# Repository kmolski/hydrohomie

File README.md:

# hydrohomie

The smart drink coaster that lets you gather, view and analyze data on your water drinking habits.

The coaster device, based on the ESP32 MCU, uses a load sensor to measure the volume of water consumed,
which is then (optionally) sent over Wi-Fi & MQTT to the web application for storage and presentation purposes.

This started out as my 5th semester project for the Microprocessor and Embedded Systems course, for which I
prepared the hardware and firmware components. The web application was created later, primarily as a means to
get some practice with new Java features and popular libraries, like Spring Integration/Security and Mockito.

Project components
------------------

- [Hardware](./hardware) - board & logic schematics in PDF & Autodesk EAGLE files
- [Firmware](./firmware) - firmware for the ESP32 chip, based on the Arduino platform
- [Web application](./web-app) - (optional) Spring Boot web app, provides coaster management & data visualization functionality

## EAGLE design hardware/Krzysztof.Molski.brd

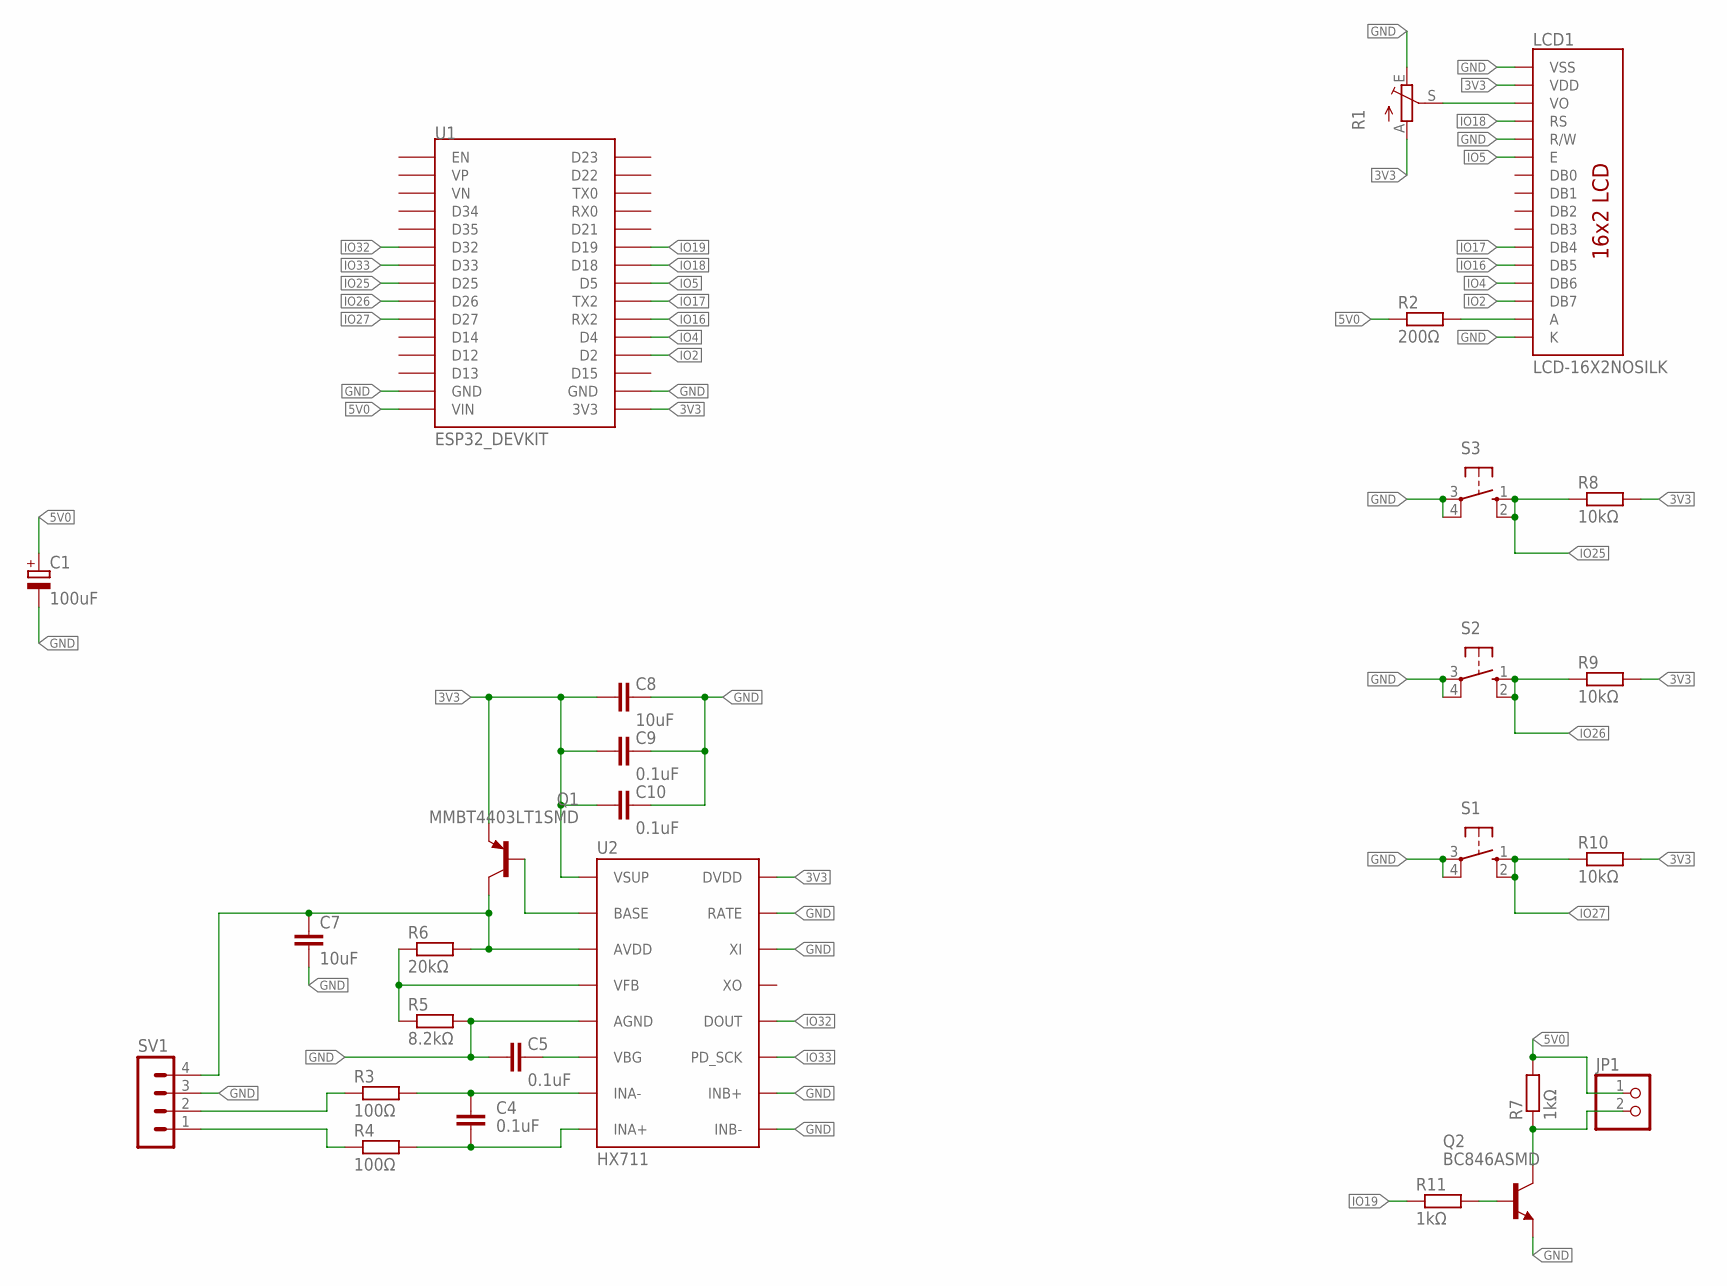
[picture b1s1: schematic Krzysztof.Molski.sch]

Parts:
C1: 100uF; CT3528
C4, C5, C9, C10: 0.1uF; C1206
C7, C8: 10uF; C1206
JP1: PINHD-1X2; 1X02
LCD1: LCD-16X2NOSILK; LCD-16X2_NOSILK
Q1: MMBT4403LT1SMD; SOT23-BEC
Q2: BC846ASMD; SOT23
R1: TRIM_EU-CA6V; CA6V
R2: 200Ω; R0805
R3, R4: 100Ω; R0805
R5: 8.2kΩ; R0805
R6: 20kΩ; R0805
R7, R11: 1kΩ; R0805
R8, R9, R10: 10kΩ; R0805
S1, S2, S3: 10-XX; B3F-10XX
SV1: MA04-1
U1: ESP32_DEVKIT
U2: HX711; SO16

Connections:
3V3: C8.2, C9.2, C10.2, LCD1.2 (VDD), Q1.E, R1.A, R8.2, R9.2, R10.2, U1.3V3, U2.1 (VSUP), U2.16 (DVDD)
5V0: C1.+, JP1.1, R2.1, R7.2, U1.VIN
GND: C1.-, C5.2, C7.2, C8.1, C9.1, C10.1, LCD1.1 (VSS), LCD1.5 (R/W), LCD1.16 (K), Q2.2 (E), R1.E, R5.2, S1.3, S1.4 (P1), S2.3, S2.4 (P1), S3.3, S3.4 (P1), SV1.3, U1.GND@1 (GND), U1.GND@2 (GND), U2.5 (AGND), U2.9 (INB-), U2.10 (INB+), U2.14 (XI), U2.15 (RATE)
IO2: LCD1.14 (DB7), U1.D2
IO4: LCD1.13 (DB6), U1.D4
IO5: LCD1.6 (E), U1.D5
IO16: LCD1.12 (DB5), U1.RX2
IO17: LCD1.11 (DB4), U1.TX2
IO18: LCD1.4 (RS), U1.D18
IO19: R11.1, U1.D19
IO25: R8.1, S3.1 (S), S3.2 (S1), U1.D25
IO26: R9.1, S2.1 (S), S2.2 (S1), U1.D26
IO27: R10.1, S1.1 (S), S1.2 (S1), U1.D27
IO32: U1.D32, U2.12 (DOUT)
IO33: U1.D33, U2.11 (PD_SCK)
unnamed: C4.1, R4.2, U2.8 (INA+)
unnamed: R3.1, SV1.2
unnamed: LCD1.15 (A), R2.2
unnamed: C4.2, R3.2, U2.7 (INA-)
unnamed: Q1.B, U2.2 (BASE)
unnamed: LCD1.3 (VO), R1.S
unnamed: Q2.1 (B), R11.2
unnamed: R4.1, SV1.1
unnamed: C5.1, U2.6 (VBG)
unnamed: C7.1, Q1.C, R6.2, SV1.4, U2.3 (AVDD)
unnamed: R5.1, R6.1, U2.4 (VFB)
unnamed: JP1.2, Q2.3 (C), R7.1

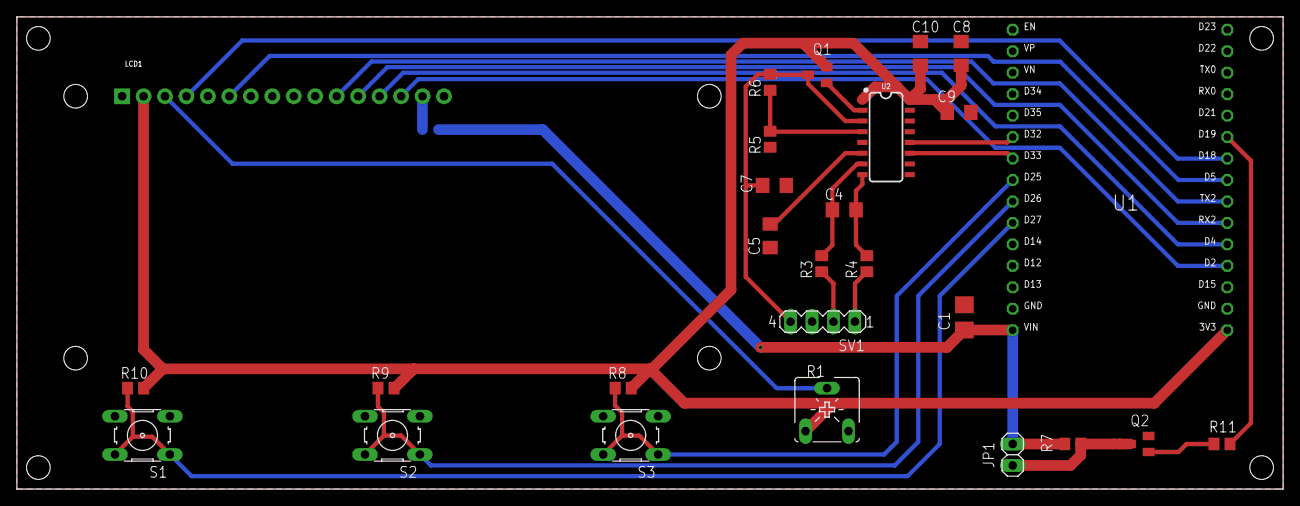
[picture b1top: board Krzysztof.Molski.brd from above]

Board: 2 copper layers, 149.9 x 55.9 mm, 28 parts (1 on the bottom side), 27 nets.

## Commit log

2021-01-20 Add Wi-Fi connection code
2021-01-23 Embedded code prototype with MQTT conn
2021-01-23 Add simple echo app for testing
2021-01-23 Add Maven config for runnable JAR
2021-01-24 Naming + text formatting changes
2021-01-27 Move load cell readings into its own task
2021-01-28 Add volume total and connection status display
2021-01-28 Use CLI args instead of secrets class in app
2021-01-31 Add inactivity measurement and buzzer control
2021-01-31 Use mutex to secure last_activity time point
2021-02-05 Add date+timestamps to MQTT echo app
2021-02-05 Fix race condition in tare request
2021-02-19 Remove unnecessary atomic from `coaster_state`
2021-04-02 Uniquely identify coaster by its MAC address
2021-04-19 Migrate the embedded project to PlatfromIO
2021-04-19 Clean up Arduino project files
2021-04-19 Use JSON payloads, reformat embedded code
2021-04-20 Add EAGLE board and schematic files
2021-04-21 Remove JSON messages for inactivity and total clear
2021-06-23 Add CAM output (Gerber+drill+assembly) board files
2021-07-28 Remove echo-app
2021-07-29 Add Spring Boot web application
2021-09-11 Update build.gradle and add entity classes
2021-09-11 Add webjars for Bootstrap, reformat source code
2021-09-11 Add basic MQTT configuration and Message class
2021-09-11 Rename Message -> CoasterMessage, rename "cancel" message to "discard"
2021-09-12 Update MQTT configuration
2021-09-12 Add MQTT device topic handler
2021-09-12 Add secrets.h file for firmware
2021-10-08 Working MQTT flow for connected->listening interaction
2021-10-10 Add initial load and inactivity info to Coaster model
2021-10-10 Modify CoasterRepository.save, add CoasterService
2021-10-10 Modify ListeningMessage, HeartbeatMessage
2021-10-10 Migrate measurements to zoned datetime, add logic for device topic messages
2021-10-10 Change ZonedDateTime to Instant
2021-10-12 Pass current time/date in arguments
2021-10-12 Update .clang-format, handle ListeningMessage in firmware
2021-10-13 Add timezones to Coaster entities, handle TZ conversion in queries
2021-10-13 Account for server time zone in daily volume calculation
2021-10-14 Adjust log messages & embedded code
2021-10-15 Add heartbeat message
2021-10-17 Fix MQTT disconnect on send, inactive_since default value
    Inbound and outbound MQTT clients now have different client IDs, ending with "-rx" and "-tx" respectively. The inactiveSince coaster field is now initialized with the current time.
2021-10-21 Improve time handling with clock DI
    CoasterRepository::create now takes an Instant parameter for inactive_since. All CoasterService methods now take Instant parameters for the current time.
2021-10-21 Reformat code, change parameter names
2021-10-21 Update last_activity on drink start in firmware.
    Following the web app change, the time since last activity will be reset when the drink is started.
2021-10-23 Extract constants and configuration into separate header files
2021-10-24 Improve MQTT reconnect handling
    Restarting the MQTT broker connection no longer hangs the user interface.
2021-10-24 Remove serial port logging, add comments
2021-10-24 Add firmware README.md with setup instructions
2021-10-24 Update firmware README.md formatting
2021-10-24 Create LICENSE
2021-10-24 Move LICENSE
2021-11-01 Organize web app classes
2021-11-01 Add admin and user account support
2021-11-02 Add custom login page template
2021-11-02 Change configuration prefix for admin account and MQTT client
2021-11-02 Center login form on the page
2021-11-14 Allow healthcheck endpoint access for all clients
2022-04-27 Update dependencies
2022-05-07 Fix circular dependency, refactor if instanceof chain
2022-06-11 Add .gitattributes & LICENSE
2022-06-15 Use Component in config classes, change security config
2022-06-16 Update Spring Boot, add Thymeleaf extras & Argon2 library
2022-06-16 Move packages, fix CSRF token in login form, use Argon2 hashing
2022-06-18 Add RootController and account view for admin
2022-06-18 Add some JavaDoc documentation
2022-06-26 Add coaster owner, create package for coaster-related classes
2022-06-26 Use records to define config properties
2022-06-26 Fix coaster package references
2022-06-26 Remove UserPrincipal
2022-07-02 Change title of login page
2022-07-02 Add user account view for admin
2022-07-02 Use records for config properties, add Lombok
2022-07-02 Add user account remove action for admin
2022-07-03 Add user enable/disable action for admin
2022-07-03 Add Spring Validation and NewUserDto
2022-07-03 Add user create form for admin
2022-07-03 Add user create form HTML template
2022-07-03 Add password confirmation validator
2022-07-03 Improve HTML templates
2022-07-10 Add change user password action for admin
2022-07-10 Add change password action for user
2022-07-11 Fix warnings in Thymeleaf templates
2022-07-11 Add JavaDocs
2022-07-14 Add JavaDocs, unit tests for AdminAccountManagementController
2022-07-16 Create GH Action for Gradle build & test
2022-07-19 Add unit tests for account package
2022-07-20 Add JavaDocs, logging & integration tests for accounts
2022-07-23 Update autogenerated coverage badge
2022-07-23 Add coverage badge (#1)
    * Update build.gradle
    * Update gradle.yml
    * Update autogenerated coverage badge
    * Update README.md
2022-07-23 Move LICENSE, update lombok.config to fix coverage
2022-07-24 Extract pagination fragment
2022-07-24 Add assigned coasters view for user, improve coverage
2022-07-26 Extract superclasses for unit & integration tests
2022-07-26 Add integration test for RootTopicHandler
2022-07-26 Add migration for coasters, Mosquitto IT base class
2022-07-26 Add integration test for DeviceTopicHandler
2022-07-28 Add confirmation for delete user action
2022-07-28 Add tests and JavaDocs for coaster assignment controller
2022-07-28 Adjust wait times in DeviceTopicHandlerIT, argon2id params
2022-08-07 Refactor RootTopicHandler, add JavaDocs
2022-08-07 Add coaster edit & remove views
2022-08-07 Refactor Java code and HTML views
2022-08-15 Add coaster measurements view, refactor
2022-08-19 Refactor MqttHandlerIT
2022-08-19 Add integration test for UserCoasterController
2022-08-19 Add unit tests, optimize UserCoasterControllerIT
2022-08-19 Add readOnly to Transactional annotations
2022-08-19 Update tests
2022-08-20 Bump version, remove JavaDoc errors
2022-08-20 Extract interfaces for service classes
2022-08-20 Add JavaDocs and logging statements
2022-08-20 Generate JavaDoc in pipeline
2022-08-20 Add board and electronic schematics
2022-08-20 Fix JavaDoc push
2022-08-20 Update JavaDoc
2022-08-21 Interface cleanup
2022-08-21 Add setup instructions for docker-compose
2022-08-21 Fix JavaDocs link
2022-08-21 Revert config change
2022-08-21 Fix application.yaml config
2022-08-21 Add top-level README.md
